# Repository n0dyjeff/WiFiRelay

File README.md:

# WiFiRelay - Wifi controlled dual relay
Dual relay controlled via WiFi. Uses ESP-07 module to allow external WiFi antenna.

### Motivation
This project was motivated by a desire to control my pool lights from my home automation system. I first attempted to use a Sonoff wifi controlled module with a custom hacked firmware. This would have been successful except that the unit is housed in the metallic NEMA enclosure for the pool control hardware which acted as a Faraday cage, preventing the wifi signal from reaching the Sonoff unit.

This project uses an ESP-07 module containing the ubiquitous ESP8266. The advantage of the ESP-07S is that in addition to a WiFi antenna printed onto the PC board, it has a connector allowing a coax to an external antenna, which can then be mounted outside the enclosure.

### Features
- Built in power supply allows direct connection to AC mains (85 ~ 305VAC). No external adapter required.
- Two isolated, independantly controlled, normally open relay contacts rated at 10 amps each.
- Connector for external WiFi antenna allows unit to be mounted within a metal enclosure.
- Over the air software updates.
- Wifi control via MQTT subscription.

### Software
(https://github.com/n0dyjeff/WifiRelay-Tasmota)

### Availability
All the documentation is here, but if you're not interested in building your own, I've built up a few of these and offered them on [Amazon](https://www.amazon.com/N0DY-WiFi-Controlled-Dual-Relay/dp/B072MKV8ZM), [ebay](http://www.ebay.com/itm/NEW-Web-Controlled-Dual-Relay-120-240-V-Smart-Home-Internal-External-Antenna-/152649721279), and [Tindie](https://www.tindie.com/products/n0dyjeff/wi-fi-controlled-dual-relay-wext-antenna-jack/). It's also available direct from my via my web site, [N0DY Electronics](https://www.n0dy.com).

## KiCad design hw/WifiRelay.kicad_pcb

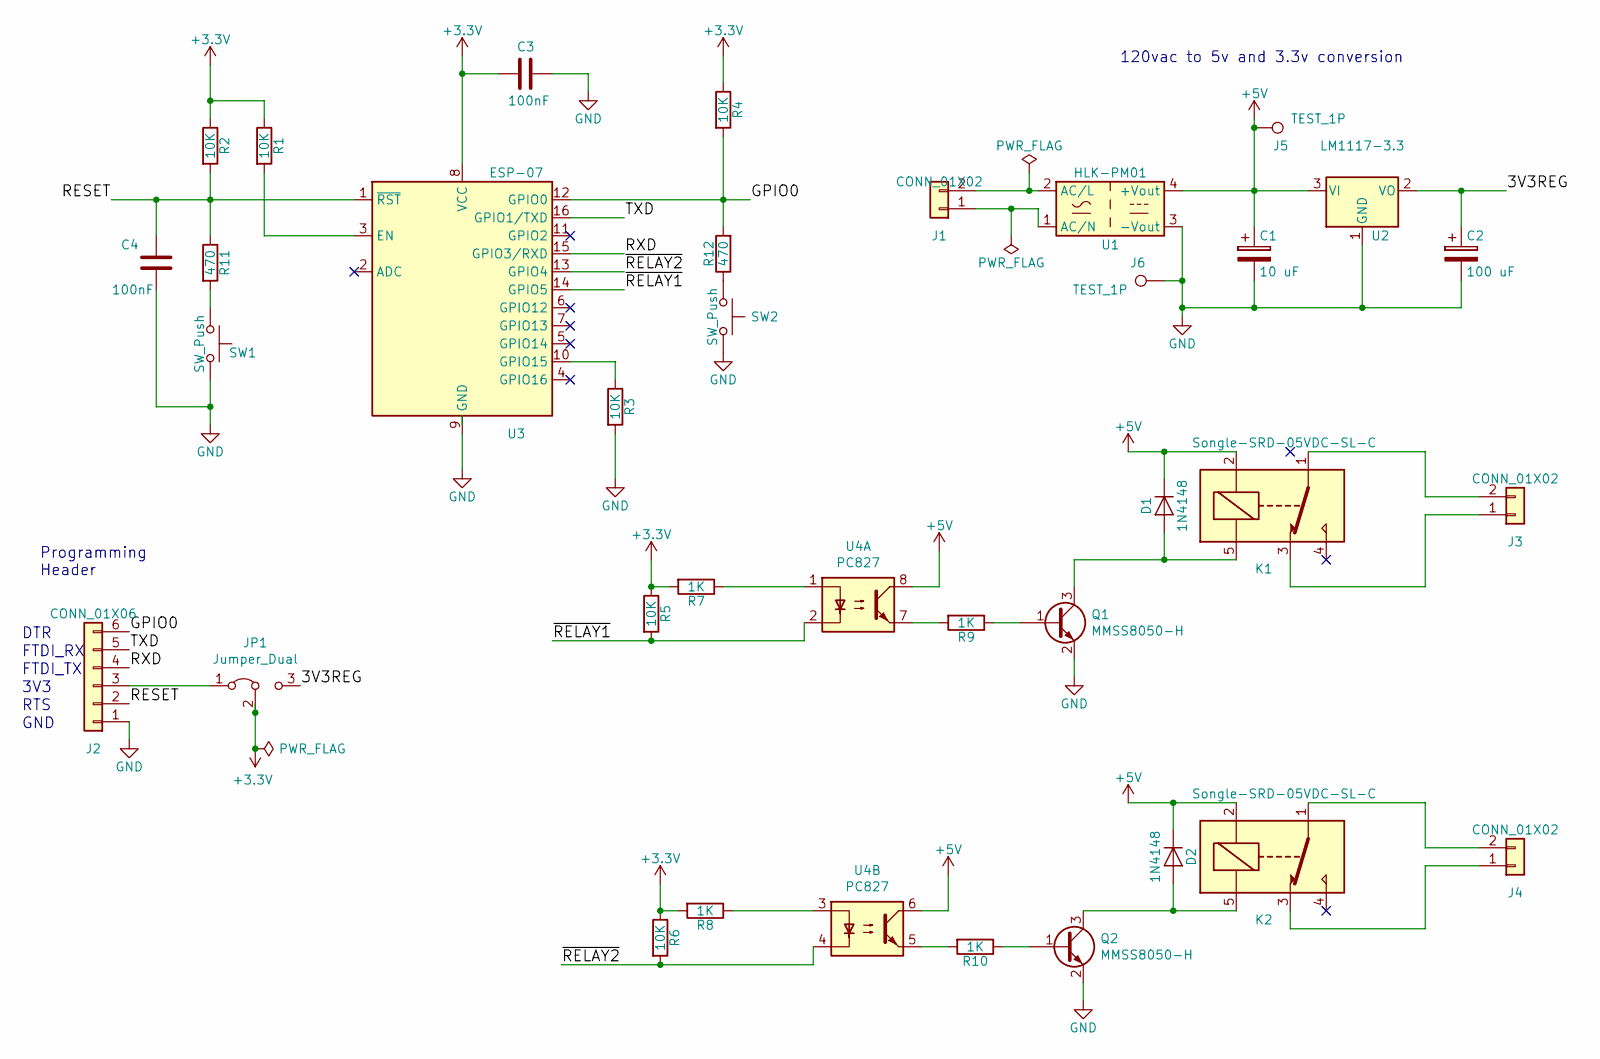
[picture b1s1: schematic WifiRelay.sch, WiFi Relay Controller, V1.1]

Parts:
C1: 10 uF; CP_EIA-3216-18_Kemet-A; MPN 293D106X0010A2TE3
C2: 100 uF; CP_EIA-3528-21_Kemet-B; MPN TL8A0107M010C
C3: 100nF; C_0805_2012Metric; MPN C0805C104K8RACTU; Mouser 80-C0805C104K8R
C4: 100nF; C_0805; MPN C0805C104K8RACTU; Mouser 80-C0805C104K8R
D1, D2: 1N4148; D_SOD-123; MPN 1N4148W-7-F; Mouser Value
J1, J4: CONN_01X02; TerminalBlock_Phoenix_MKDS-1,5-2_1x02_P5.00mm_Horizontal; MPN OSTYC022150
J2: CONN_01X06; PinHeader_1x06_P2.54mm_Vertical; MPN None
J3: CONN_01X02; TerminalBlock_Pheonix_MKDS1.5-2pol; MPN OSTYC022150
J5, J6: TEST_1P; PinHeader_1x01_P2.54mm_Vertical
JP1: Jumper_Dual; PinHeader_1x03_P2.54mm_Vertical; MPN Value; Mouser Value
K1, K2: Songle-SRD-05VDC-SL-C; Relay_SPDT_SANYOU_SRD_Series_Form_C; MPN Value; Mouser Value
Q1, Q2: MMSS8050-H; SOT-23
R1, R2, R3, R4, R5, R6: 10K; R_0805_2012Metric; MPN CRG0805F10K; Mouser 279-CRG0805F10K/10
R7, R8: 1K; R_0805_2012Metric; MPN CRG0805F1K0; Mouser Value
R9, R10: 1K; R_0805_2012Metric; MPN CRG0805F1K0
R11, R12: 470; R_0805_2012Metric; MPN CRG0805F470R; Mouser Value
SW1, SW2: SW_Push; SW_SPST_TL3342; MPN B3U-1000P; Mouser Value
U1: HLK-PM01; MPN IRM-02-05; Mouser 709-IRM02-5
U2: LM1117-3.3; SOT-223-3_TabPin2; MPN LM1117MPX-3.3/NOPBCT-ND; Mouser Value
U3: ESP-07
U4: PC827; SOIC-8; MPN Value; Mouser Value

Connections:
+3V3: C3.2, JP1.2 (C), R1.1, R2.1, R4.1, R5.1, R6.1, R7.2, R8.2, U3.8 (VCC)
+5V: C1.1, D1.1 (K), D2.1 (K), J5.1, K1.2, K2.2, U1.4 (+Vout), U2.3 (VI), U4.6, U4.8
/3V3REG: C2.1, JP1.3 (B), U2.2 (VO)
/GPIO0: J2.6, R4.2, R12.2, U3.12 (GPIO0)
/RESET: C4.1, J2.2, R2.2, R11.1, U3.1 (~RST)
/RXD: J2.4, U3.15 (GPIO3/RXD)
/TXD: J2.5, U3.16 (GPIO1/TXD)
/~RELAY1: R5.2, U3.14 (GPIO5), U4.2
/~RELAY2: R6.2, U3.13 (GPIO4), U4.4
GND: C1.2, C2.2, C3.1, C4.2, J2.1, J6.1, Q1.2 (E), Q2.2 (E), R3.2, SW1.2, SW2.2, U1.3 (-Vout), U2.1 (GND), U3.9 (GND)
unnamed: D1.2 (A), K1.5, Q1.3 (C)
unnamed: D2.2 (A), K2.5, Q2.3 (C)
unnamed: J1.1, U1.1 (AC/N)
unnamed: J1.2, U1.2 (AC/L)
unnamed: J2.3, JP1.1 (A)
unnamed: J3.1, K1.3
unnamed: J3.2, K1.1
unnamed: J4.1, K2.3
unnamed: J4.2, K2.1
unnamed: Q1.1 (B), R9.1
unnamed: Q2.1 (B), R10.1
unnamed: R1.2, U3.3 (EN)
unnamed: R3.1, U3.10 (GPIO15)
unnamed: R7.1, U4.1
unnamed: R8.1, U4.3
unnamed: R9.2, U4.7
unnamed: R10.2, U4.5
unnamed: R11.2, SW1.1
unnamed: R12.1, SW2.1

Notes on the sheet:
3V3
RTS
FTDI_RX
FTDI_TX
DTR
GND
120vac to 5v and 3.3v conversion
Programming Header

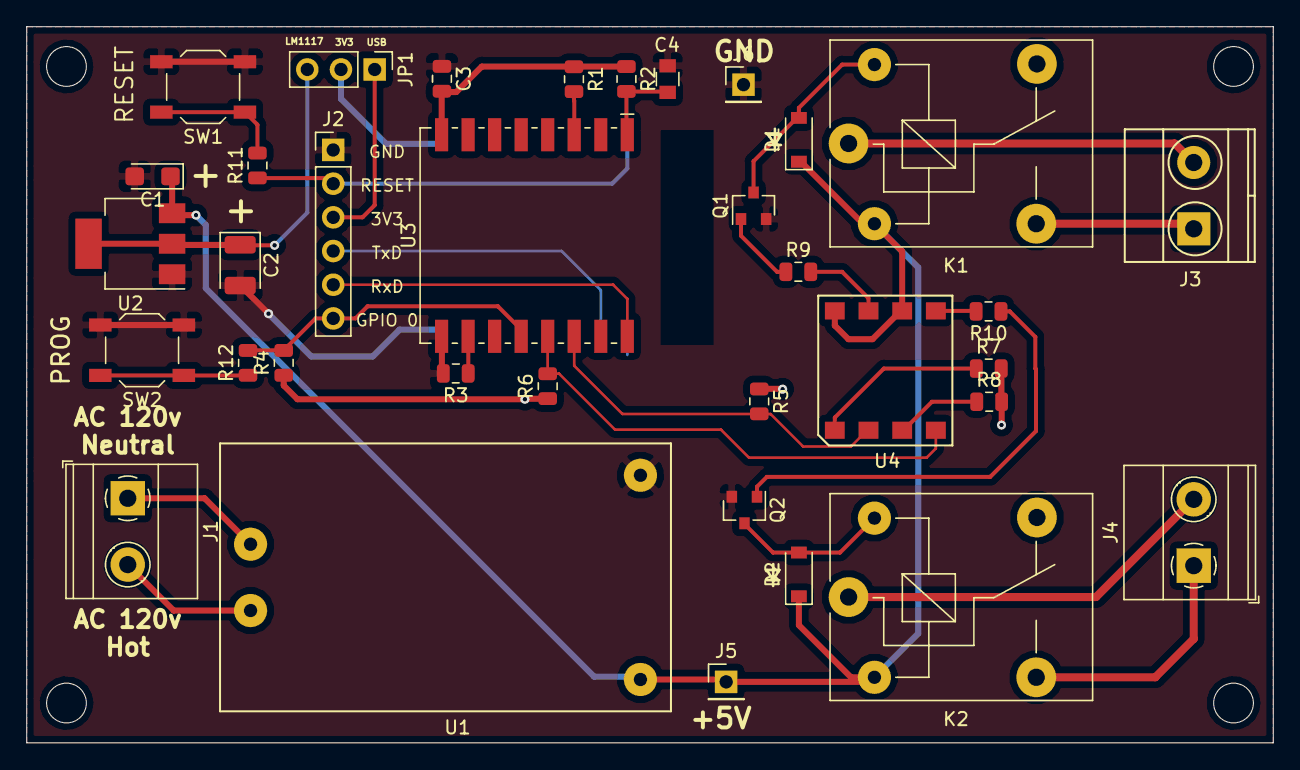
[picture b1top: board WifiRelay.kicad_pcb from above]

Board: 2 copper layers, 94.0 x 54.0 mm, 35 parts (0 on the bottom side), 29 nets.

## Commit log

2017-05-03 Initial file upload
2017-05-03 Added missing files
2017-05-09 Added ESP libraries
2017-05-25 Renamed from 'Pool Lights' to WifiRelay' and added template for drilling the box
2017-05-26 Moved file
2017-06-01 V1.1 hardware with low cost components Dropped LEDs Added +5v test point Changed two single optos for 1 dual Changed relay, +5v AC/DC conv, and 100uF parts footprints
2017-06-17 Updates to board test, schematic title block, 3D models
2017-07-04 Silkscreen updates to programming header, changed 3.3v power jumper to two positions
2017-07-05 Added user manuals
2017-07-11 Added pdf version of HW Users Guide
2017-08-16 Update README.md
    Corrected to reflect use of ESP-07 with both onboard and external antenna
2017-08-16 Added references to GitHub
2017-08-23 Minor edits for consistency
2017-08-23 Readable schematic
2018-02-20 Adding kicad libraries
2018-02-20 Don't ignore .gitignore
2018-02-20 Change MQTT server to neptune
2018-02-20 Added www.n0dy.com site to README.md. Stop tracking PrivateMQTT.h and PrivateWifi.h
2018-02-20 Added example PrivateMQTT and PrivateWifi files
2018-02-20 Removed PrivateMQTT.h and PrivateWifi.h
2018-12-26 Bring SimpleTimer library into tracked code
2018-12-29 Revert "Bring SimpleTimer library into tracked code"
    This reverts commit 778c7b7149f805f02c32ed545d85f82c4505fd21.
2019-01-07 Fixed lint / compiler gripe with const char *
2019-01-12 Moved WifiRelay.lib symbol lib into project
2019-01-12 Ignore rescue directories and binary object files.
2019-01-12 Adjusted library paths Remapped symbols to legacy libraries for KiCad 5 compatibility
2019-01-12 Changes to improve version comparisons in KiCad See https://jnavila.github.io/plotkicadsch/
2019-01-12 Fixed library paths documents directory on drive C
2019-01-12 Reverted WifiRelay.sch
2019-01-12 Changed to Unix line endings
2019-01-12 Remapped symbols into V5 libraries
2019-01-12 Unix line endings
2019-01-12 Added build notes and a batch file to flash BoardTest
2019-01-13 Updated symbol and footprint libraries to use KiCad 5 versions.
2019-01-13 Updated symbol for MMSS8050-H transistor to use new KiCad library symbol
2019-01-13 Added 3D shape for relays
2019-01-13 Added 3D shapes for 2 pin terminal blocks J1, J3 and J4
2019-01-13 Added 3D symbol for ESP-07. Corrected connections to J1 and J4 (broken in previous revision)
2019-01-13 Added datasheet for LM1117-3.3
